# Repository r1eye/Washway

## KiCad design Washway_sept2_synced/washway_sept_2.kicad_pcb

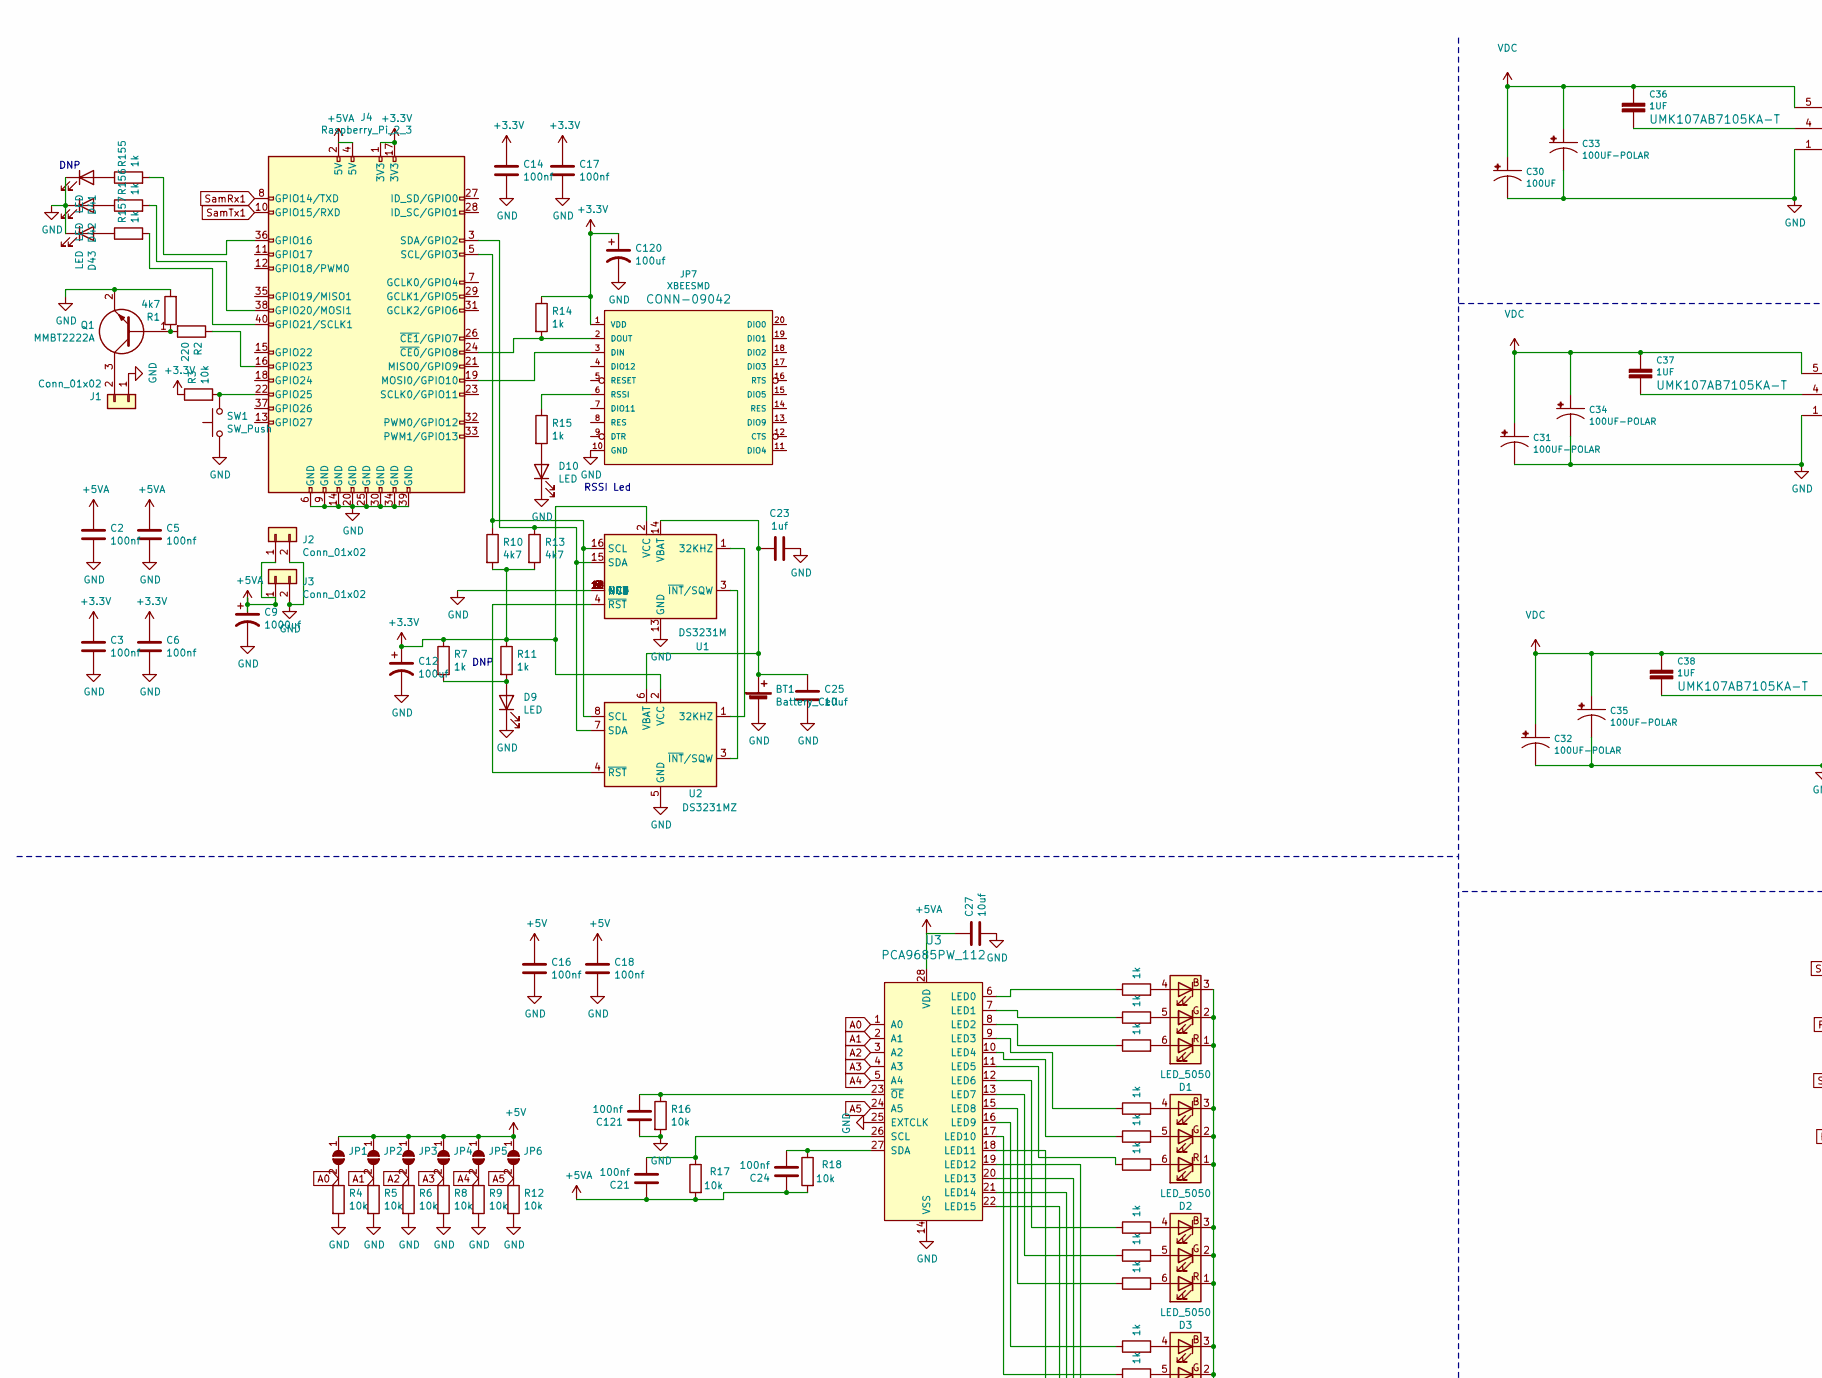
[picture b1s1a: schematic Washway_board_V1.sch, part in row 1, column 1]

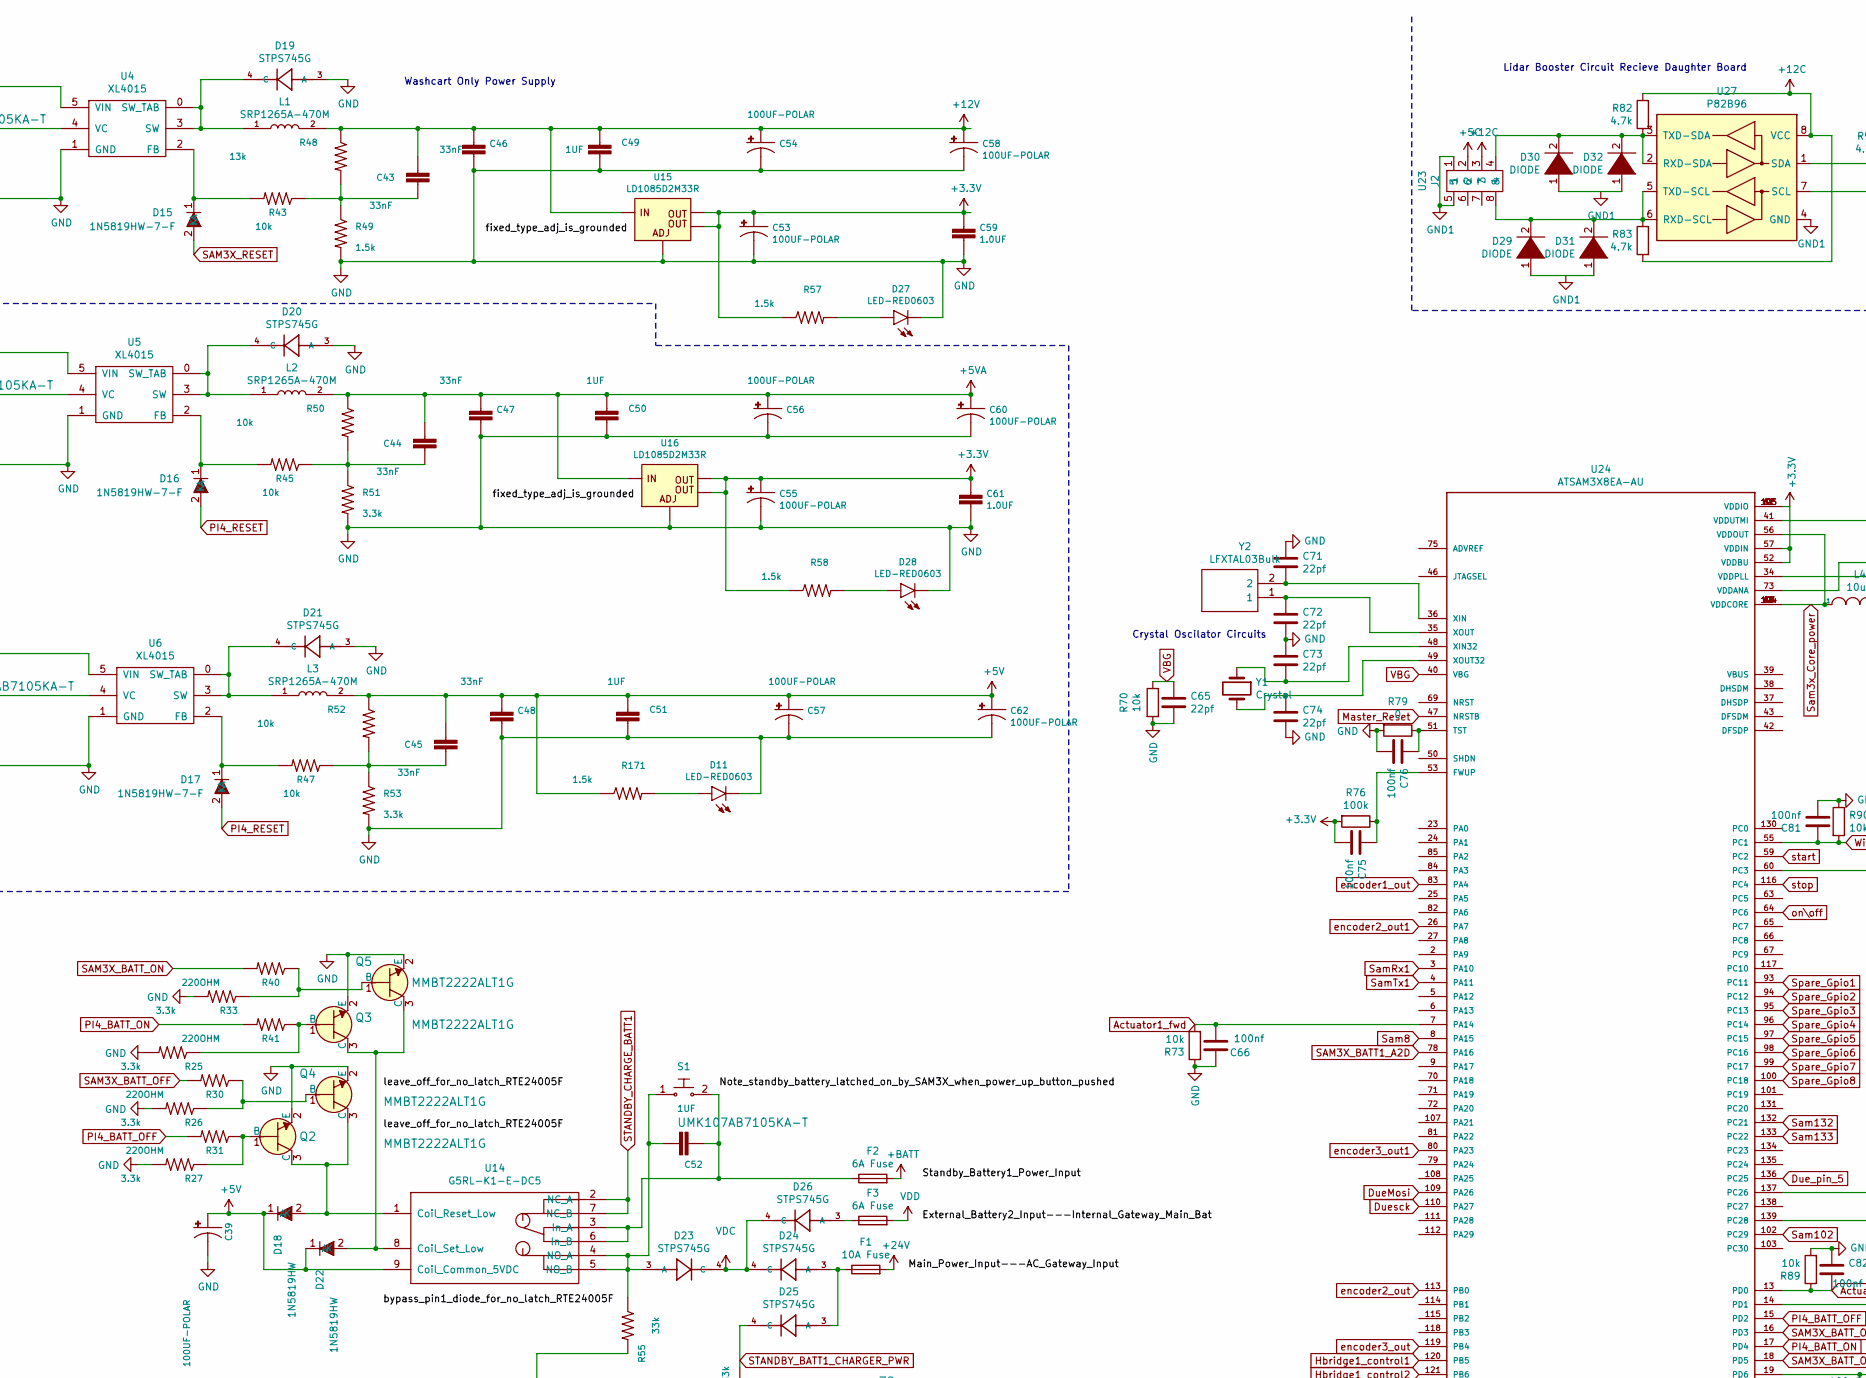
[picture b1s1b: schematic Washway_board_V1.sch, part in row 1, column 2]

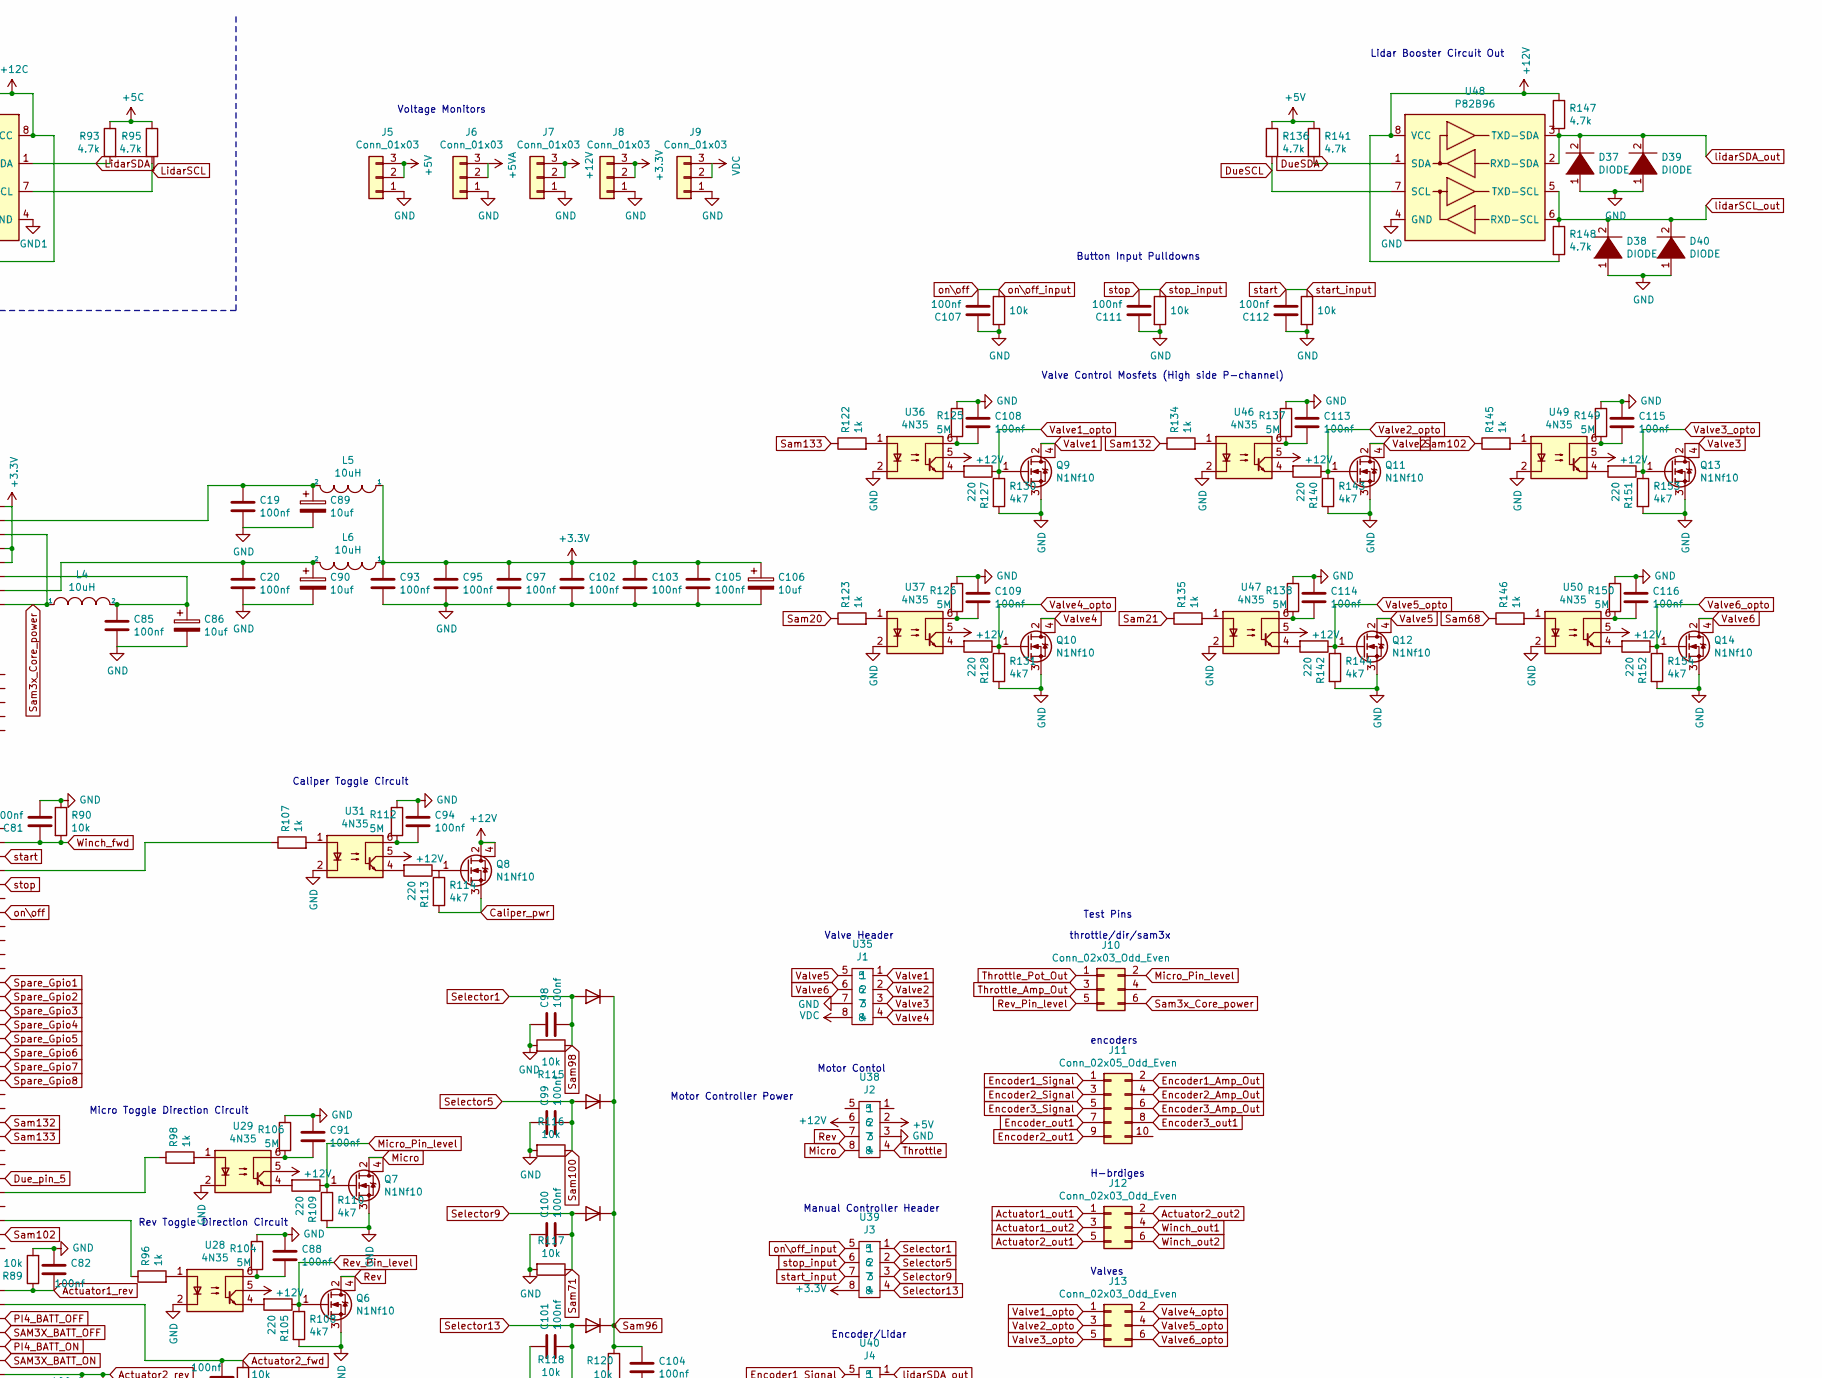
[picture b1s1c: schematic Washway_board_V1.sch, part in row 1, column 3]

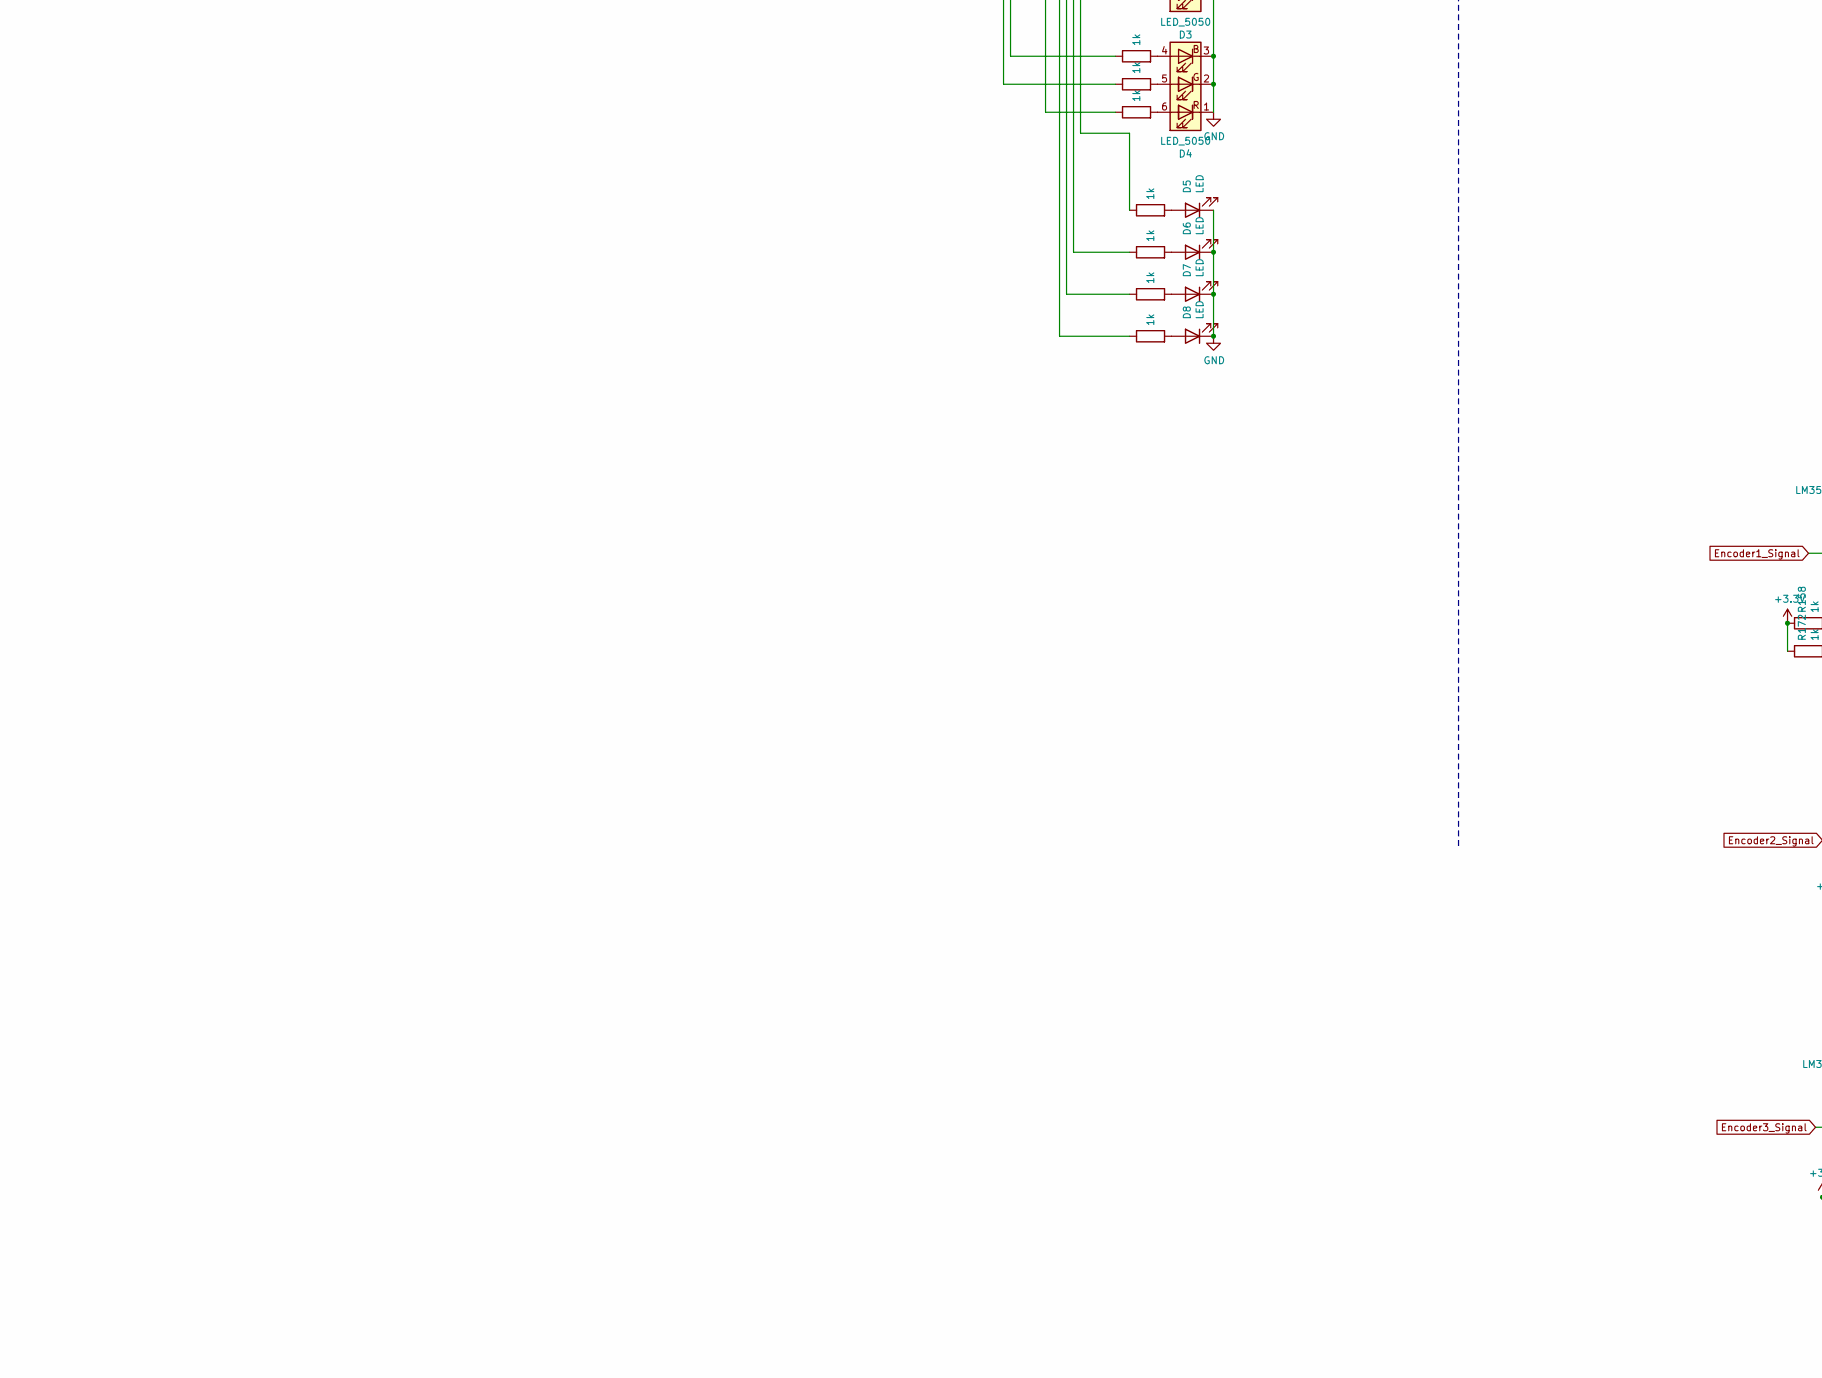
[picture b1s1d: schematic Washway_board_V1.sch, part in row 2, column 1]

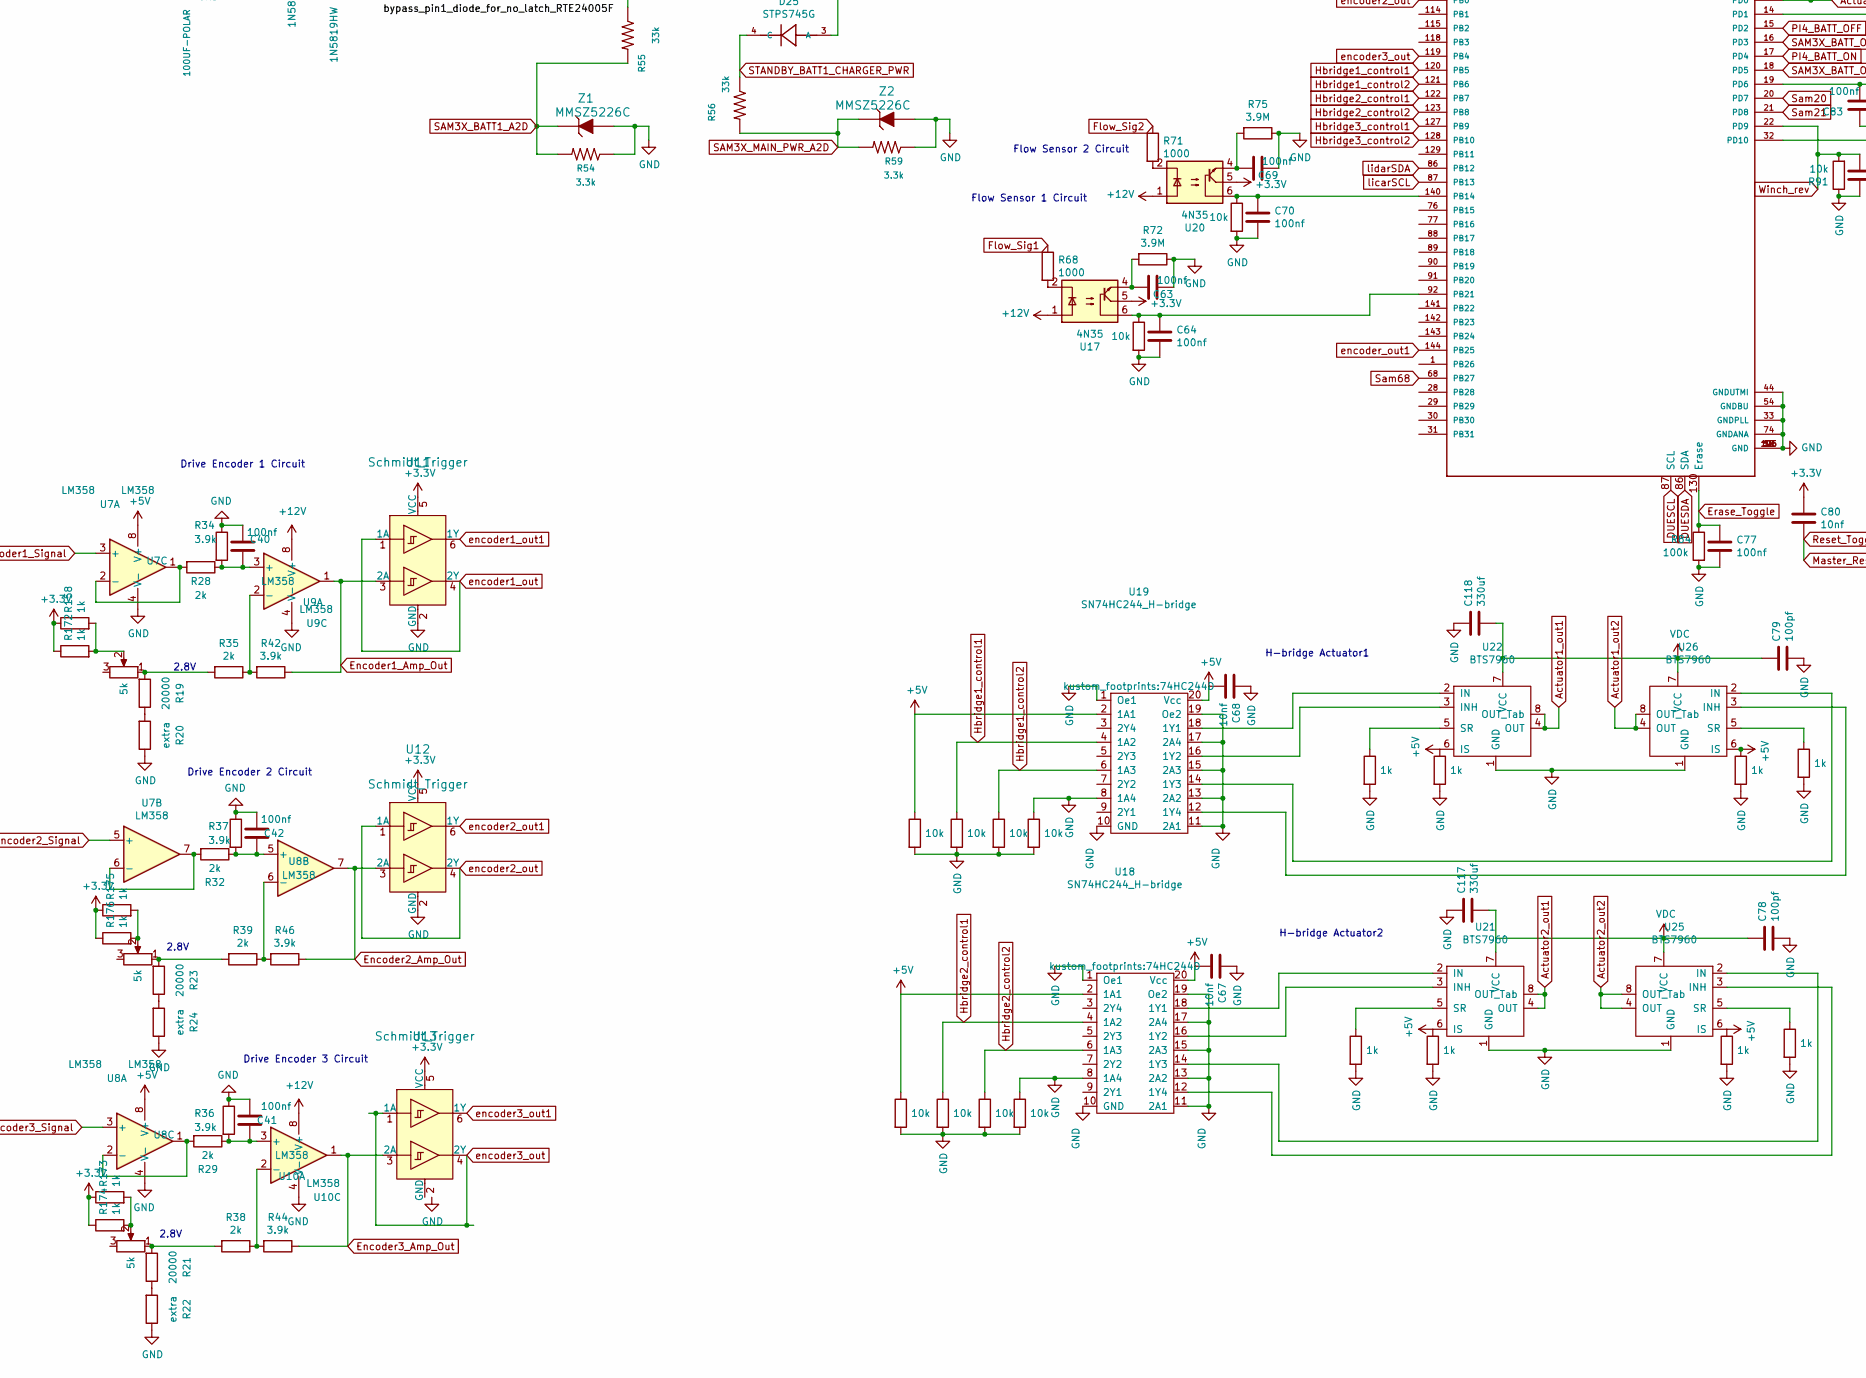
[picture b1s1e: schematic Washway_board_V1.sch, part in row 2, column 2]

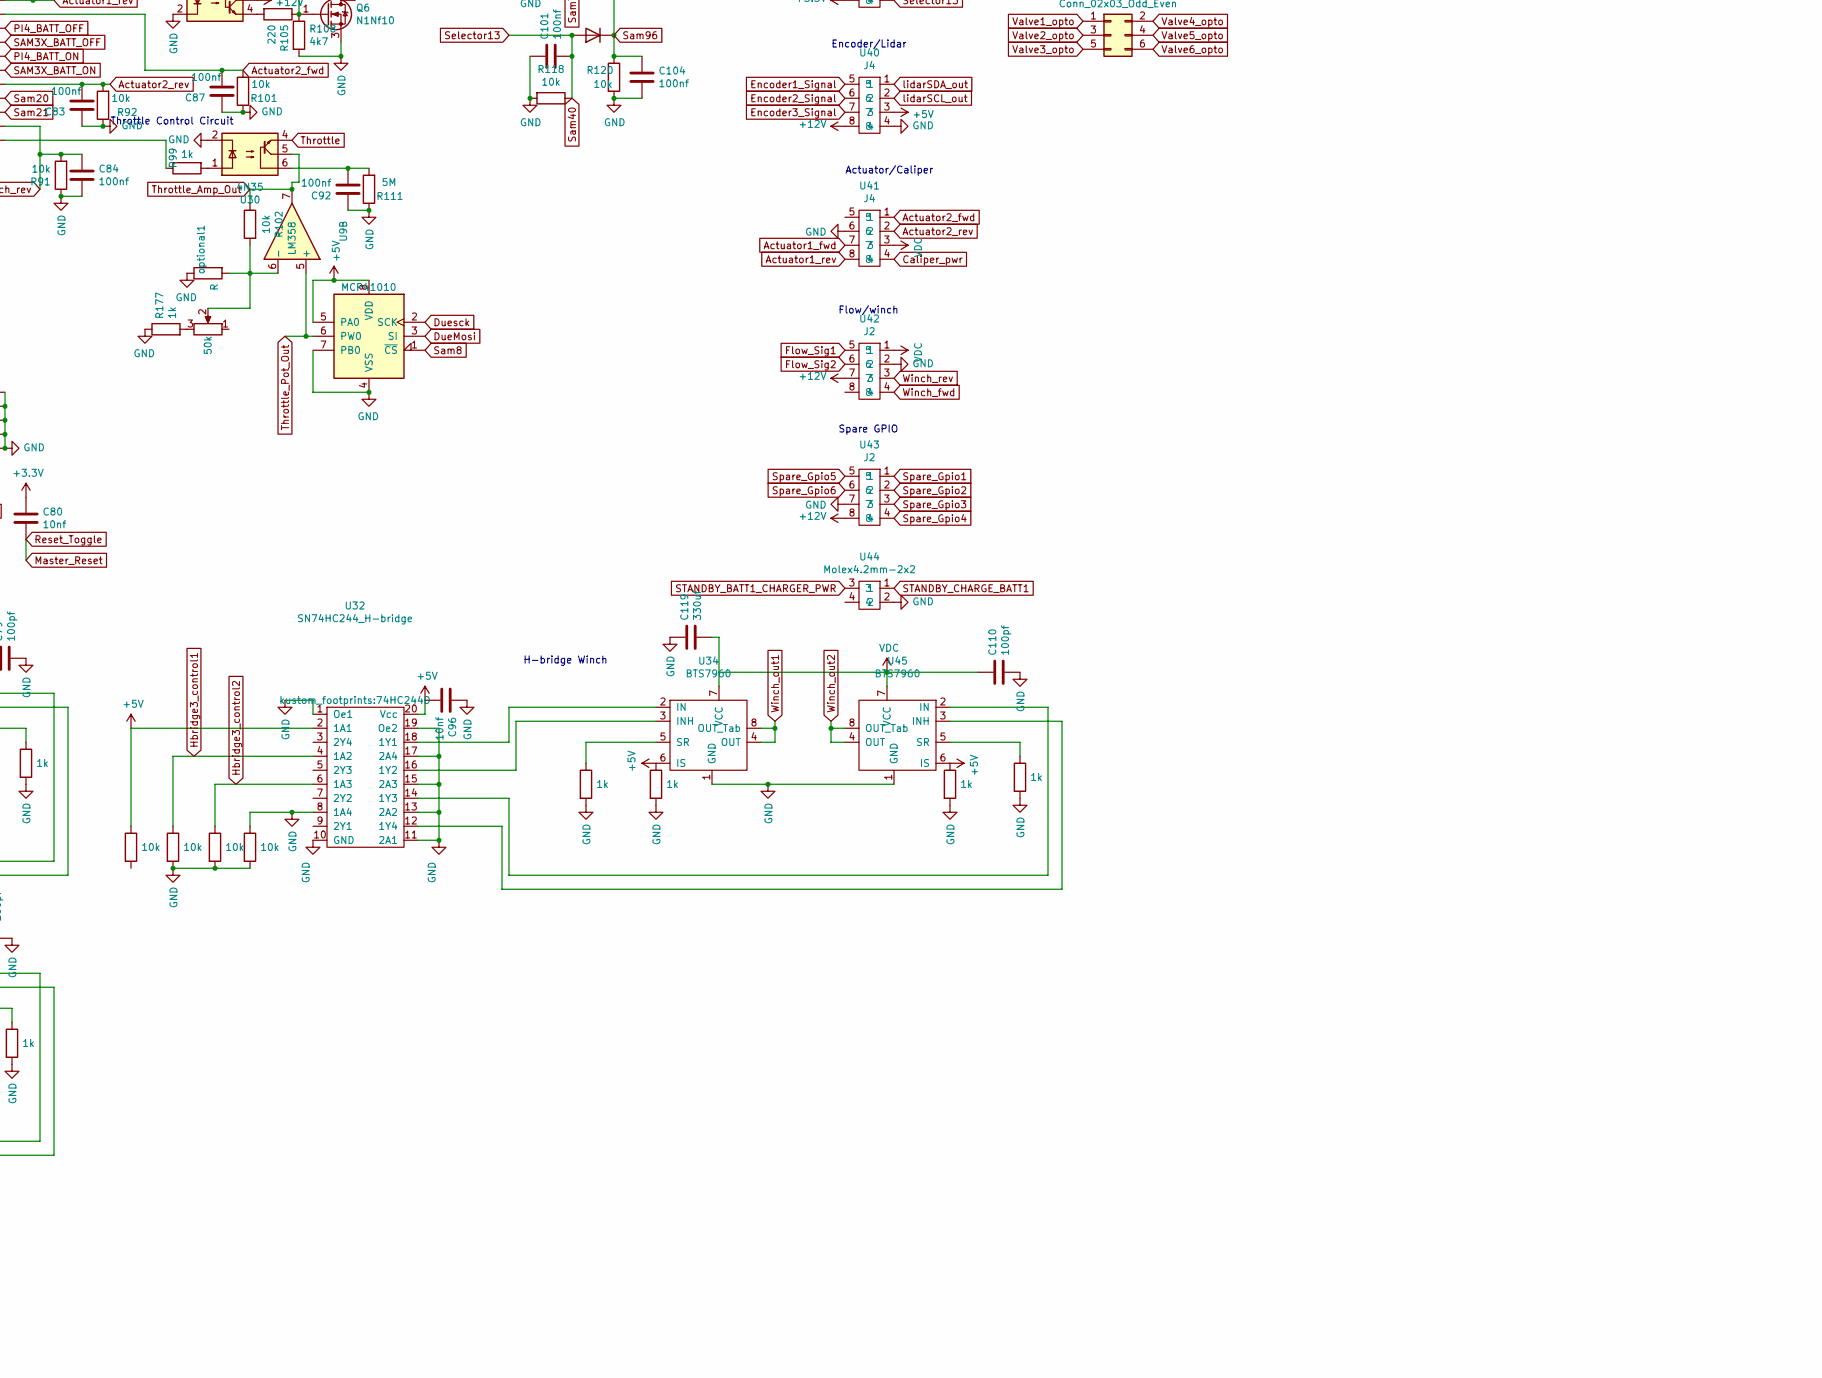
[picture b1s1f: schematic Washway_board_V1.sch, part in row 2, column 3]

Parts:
BT1: Battery_Cell; 2025_bat_horizontal
C2, C3, C5, C6, C14, C16, C17, C18, C20, C21, C24, C40, C41, C42, C63, C64, C66, C69, C70, C75, C76, C77, C81, C82, C83, C84, C85, C87, C88, C91, C92, C93, C94, C95, C97, C98, C99, C100, C101, C102, C103, C104, C105, C107, C108, C109, C111, C112, C113, C114, C115, C116, C121: 100nf; 100nf_0805
C9: 1000uf; CP_Radial_D8.0mm_P3.80mm
C12, C120: 100uf; 100uf_CP_Radial_D10.0mm_P5.00mm
C19: 100nf; 100uf_CP_Radial_D10.0mm_P5.00mm
C23: 1uf; 1uf_0805
C25, C106: 10uf; 10uf_2816_7142_3.20x4.45
C27, C86, C89, C90: 10uf; 10uf_0805
C30: 100UF; 100uf_CP_Radial_D10.0mm_P5.00mm
C31, C32, C33, C34, C35, C39, C53, C54, C55, C56, C57, C58, C60, C62: 100UF-POLAR; 100uf_CP_Radial_D10.0mm_P5.00mm
C36, C37, C38, C49, C50, C51, C52: 1UF; 1uf_0805
C43, C44, C45, C46, C47, C48: 33nF; 33nf_0805
C59, C61: 1.0UF; 1uf_0805
C65, C71, C72, C73, C74: 22pf; 22pf_0805
C67, C68, C80, C96: 10nf; 10nf_0805
C78, C79, C110: 100pf; 100pf_0805
C117, C118, C119: 330uf; 330uf_CP_Radial_D10.0mm_P5.00mm
D1, D2, D3, D4: LED_5050; LED_RGB_5050-6
D5, D6, D7, D8, D9, D41, D42, D43: LED; Led_0805
D10: LED; LED_D5.0mm
D11, D27, D28: LED-RED0603; Led_0805
D15, D16, D17: 1N5819HW-7-F; D_SMA_SS510; MPN 1N5819HW-7-F; Digi-Key_PN 1N5819HW-FDICT-ND
D18: 1N5819HW; D_SMA_SS510; MPN 1N5819HW-7-F; Digi-Key_PN 1N5819HW-FDICT-ND
D19, D20, D21, D23, D24, D25, D26: STPS745G; TO254P1543X460-3N
D22: 1N5819HW; D_SMA; MPN 1N5819HW-7-F; Digi-Key_PN 1N5819HW-FDICT-ND
D29, D30, D31, D32, D37, D38, D39, D40: DIODE; D_SMA_SS510
D33, D34, D35, D36: D; D_SMA_SS510
F1: 10A Fuse; Fuse_2512_6332Metric
F2, F3: 6A Fuse; Fuse_2512_6332Metric
J1: Conn_01x02; PinHeader_1x02_P2.00mm_Vertical
J2: Conn_01x02; fan_2.00mm_header
J3: Conn_01x02; fan_header_2.54header
J4: Raspberry_Pi_2_3; pi_connector
J5, J6: Conn_01x03; Voltage_5v_header
J7: Conn_01x03; Voltage_12v_header
J8: Conn_01x03; Voltage_3.3v_header
J9: Conn_01x03; Voltage_24v_header
J10: Conn_02x03_Odd_Even; throttle_dir_sam3x
J11: Conn_02x05_Odd_Even; Encoders_tester
J12: Conn_02x03_Odd_Even; H_bridges_tester
J13: Conn_02x03_Odd_Even; Valves_tester
JP1, JP2, JP3, JP4, JP5, JP6: 0_ohm_0805
JP7: XBEESMD; xbee_gateway_header
L1, L2, L3: SRP1265A-470M; IND_SRP1265A-330M
L4, L5, L6: 10uH; 10uH_1812_4532
P1, P2, P3: 5k; 5k_trim
P4: 50k; 50k_trim
Q1: MMBT2222A; SOT-23-3; Mouser Part Number 512-MMBT2222A
Q2, Q3, Q4, Q5: MMBT2222ALT1G; SOT-23-3; MPN MMBT2222ALT1G; Digi-Key_PN MMBT2222ALT1GOSCT-ND
Q6, Q7, Q8, Q9, Q10, Q11, Q12, Q13, Q14: N1Nf10; N1Nf10_SOT23
R1, R10, R13, R108, R110, R114, R130, R131, R143, R144, R153, R154: 4k7; 4.7k_0805
R2, R105, R109, R113, R127, R128, R140, R142, R151, R152: 220; 220_0805
R3, R4, R5, R6, R8, R9, R12, R16, R17, R18, R43, R45, R47, R50, R52, R60, R61, R62, R63, R64, R65, R66, R67, R69, R70, R73, R74, R89, R90, R91, R92, R94, R97, R100, R101, R102, R103, R115, R116, R117, R118, R120, R129, R133, R139: 10k; 10k_0805
R7, R11, R14, R15, R77, R78, R80, R81, R85, R86, R87, R88, R96, R98, R99, R107, R119, R121, R122, R123, R124, R132, R134, R135, R145, R146, R155, R156, R157, R158, R159, R160, R161, R162, R163, R164, R165, R166, R167, R168, R169, R170, R172, R173, R174, R175, R176, R177, R178, R179, R180, R181: 1k; 1k_0805
R19, R21, R23: 20000; 20k_0805
R20, R22, R24: extra; extra_0805
R25, R26, R27, R33, R51, R53, R54, R59: 3.3k; 3.3k_0805
R28, R29, R32, R35, R38, R39: 2k; 2k_0805
R30, R31, R40, R41: 220OHM; 220_0805
R34, R36, R37, R42, R44, R46: 3.9k; 3.9k_0805
R48: 13k; 13k_0805
R49, R57, R58, R171: 1.5k; 1.5k_0805
R55, R56: 33k; 33k_0805
R68, R71: 1000; 1k_0805
R72: 3.9M; 3.9k_0805
R75: 3.9M; 3.9M_0805
R76, R84: 100k; 100k_0805
R79: 0; 0_ohm_0805
R82, R83, R93, R95, R136, R141, R147, R148: 4.7k; 4.7k_0805
R104, R106, R111, R112, R125, R126, R137, R138, R149, R150: 5M; 5M_0805
S1: GPTS203211B; on_button; MPN GPTS203211B; Digi-Key_PN CW181-ND
SW1: SW_Push; Switch_Tactile_SMD_4.5x4.5mm_TL3315NF160Q
U1: DS3231M
U2: DS3231MZ; DS323
U3: PCA9685PW_112; TSSOP-28_W4.40mm; MPN PCA9685PW,112; Digi-Key_PN 568-8366-5-ND
U4, U5, U6: XL4015; xl4015
U7, U8, U9, U10: LM358; SOIC8_150MIL
U11, U12, U13: Schmidt_Trigger; Schmidt_trigger; MPN SN74LVC2G17DBVR; Digi-Key_PN 296-13012-1-ND
U14: G5RL-K1-E-DC5
U15, U16: LD1085D2M33R; D2PAK_M
U17, U20, U28, U29, U30, U31, U36, U37, U46, U47, U49, U50: 4N35; 4N35_smd
U18, U19, U32: SN74HC244_H-bridge; 74HC244D
U21, U22, U25, U26, U34, U45: BTS7960
U23, U38, U42, U43: J2; Molex_jr_4.2_2x4
U24: ATSAM3X8EA-AU; QFP50P2200X2200X145-144N
U27, U48: P82B96
U33: MCP41010; mcp413
U35: J1; Molex_jr_4.2_2x4
U39: J3; Molex_jr_4.2_2x4
U40, U41: J4; Molex_jr_4.2_2x4
U44: Molex4.2mm-2x2; 2X2_molex
Y1: Crystal; cfs-206_crystal
Y2: LFXTAL03Bulk; Lfxtal_crystal; Mouser Part Number 449-LFXTAL058383BULK
Z1, Z2: MMSZ5226C; MMSZ5226c_3.3V_zener; MPN MMSZ5231B-7-F; Digi-Key_PN MMSZ5231B-FDICT-ND
optional1: R; R_0805_2012Metric

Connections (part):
+3V3: C3.1, C6.1, C12.1, C14.1, C17.1, C53.1 (+), C55.1 (+), C59.1, C61.1, C75.2, C80.1, C93.1, C95.1, C97.1, C102.1, C103.1, C105.1, C106.1, C120.1, J4.1 (3V3), J4.17 (3V3), J8.2, J8.3, JP7.1 (VDD), L5.1, L6.1, R3.1, R7.1, R10.2, R11.1, R13.2, R14.1, R57.1, R58.1, R76.2, R158.1, R172.1, R173.1, R174.1, R175.1, R176.1, U1.2 (VCC), U2.2 (VCC), U11.5 (VCC), U12.5 (VCC), U13.5 (VCC), U15.2 (OUT), U16.2 (OUT), U17.5, U20.5, U24.11 (VDDIO), U24.52 (VDDBU), U24.57 (VDDIN), U24.62 (VDDIO), U24.105 (VDDIO), U24.125 (VDDIO), U39.8
+5C: R93.1, R95.1, U23.2
+5V: C16.1, C18.1, C39.1 (+), C45.1, C48.1, C51.1, C57.1 (+), C62.1 (+), C67.2, C68.2, C96.2, D18.1 (K), D22.1 (K), J5.2, J5.3, JP1.1 (A), JP2.1 (A), JP3.1 (A), JP4.1 (A), JP5.1 (A), JP6.1 (A), L3.2, R52.1, R60.1, R61.1, R80.1, R81.1, R85.1, R86.1, R94.1, R121.1, R124.1, R136.1, R141.1, R171.1, U7.8 (V+), U8.8 (V+), U14.9 (Coil_Common_5VDC), U18.2 (1A1), U18.20 (Vcc), U19.2 (1A1), U19.20 (Vcc), U21.6 (IS), U22.6 (IS), U25.6 (IS), U26.6 (IS), U32.2 (1A1), U32.20 (Vcc), U33.5 (PA0), U33.8 (VDD), U34.6 (IS), U38.2, U40.3, U45.6 (IS)
+5VA: C2.1, C5.1, C9.1, C21.1, C24.1, C27.1, C44.1, C47.1, C50.1, C56.1 (+), C60.1 (+), J2.1, J3.1, J4.2 (5V), J4.4 (5V), J6.2, J6.3, L2.2, R17.2, R18.2, R50.1, U3.28 (VDD), U16.3 (IN)
+12C: R82.1, R83.2, U23.3, U27.8 (VCC)
+12V: C43.1, C46.1, C49.1, C54.1 (+), C58.1 (+), J7.2, J7.3, L1.2, Q8.2 (D), Q8.4 (Tab), R48.1, R147.1, R148.2, U9.8 (V+), U10.8 (V+), U15.3 (IN), U17.1, U20.1, U28.5, U29.5, U31.5, U36.5, U37.5, U38.6, U40.8, U42.7, U43.8, U46.5, U47.5, U48.8 (VCC), U49.5, U50.5
+24V: F1.2
+BATT: F2.2
A0: JP1.2 (B), R4.1, U3.1 (A0)
A1: JP2.2 (B), R5.1, U3.2 (A1)
A2: JP3.2 (B), R6.1, U3.3 (A2)
A3: JP4.2 (B), R8.1, U3.4 (A3)
A4: JP5.2 (B), R9.1, U3.5 (A4)
A5: JP6.2 (B), R12.1, U3.24 (A5)
Actuator1_fwd: C66.2, R73.2, U24.7 (PA14), U41.7
Actuator1_out1: J12.1, U22.4 (OUT), U22.8 (OUT_Tab)
Actuator1_out2: J12.3, U26.4 (OUT), U26.8 (OUT_Tab)
Actuator1_rev: C82.2, R89.1, U24.13 (PD0), U41.8
Actuator2_fwd: C87.2, R101.2, U24.14 (PD1), U41.1
Actuator2_out1: J12.5, U21.4 (OUT), U21.8 (OUT_Tab)
Actuator2_out2: J12.2, U25.4 (OUT), U25.8 (OUT_Tab)
Actuator2_rev: C83.2, R92.2, U24.19 (PD6), U41.2
Caliper_pwr: Q8.3 (S), R114.2, U41.4
DueMosi: U24.109 (PA26), U33.3 (SI)
DueSCL: R136.2, U48.7 (SCL)
DueSDA: R141.2, U48.1 (SDA)
Due_pin_5: U24.136 (PC25)
Duesck: U24.110 (PA27), U33.2 (SCK)
Encoder1_Amp_Out: J11.2, R42.1, U9.1, U11.3 (2A)
Encoder1_Signal: J11.1, U7.3 (+), U40.5
Encoder2_Amp_Out: J11.4, R46.1, U8.7, U12.3 (2A)
Encoder2_Signal: J11.3, U7.5 (+), U40.6
Encoder2_out1: J11.9
Encoder3_Amp_Out: J11.6, R44.1, U10.1, U13.3 (2A)
Encoder3_Signal: J11.5, U8.3 (+), U40.7
Encoder3_out1: J11.8
Encoder_out1: J11.7
Flow_Sig1: R68.1, U42.5
Flow_Sig2: R71.1, U42.6
GND: BT1.2 (-), C2.2, C3.2, C5.2, C6.2, C9.2, C12.2, C14.2, C16.2, C17.2, C18.2, C19.2, C20.2, C23.1, C25.2, C27.2, C30.2 (-), C31.2 (-), C32.2 (-), C33.2 (-), C34.2 (-), C35.2 (-), C39.2 (-), C40.2, C41.2, C42.2, C46.2, C47.2, C48.2, C49.2, C50.2, C51.2, C53.2 (-), C54.2 (-), C55.2 (-), C56.2 (-), C57.2 (-), C58.2 (-), C59.2, C60.2 (-), C61.2, C62.2 (-), C63.2, C64.2, C65.2, C66.1, C67.1, C68.1, C69.2, C70.2, C71.1, C72.1, C73.1, C74.1, C76.2, C77.2, C78.2, C79.2, C81.2, C82.1, C83.1, C84.2, C85.2, C86.2, C87.1, C88.1, C89.2, C90.2, C91.1, C92.1, C93.2, C94.1, C95.2, C96.1, C97.2, C98.1, C99.1, C100.1, C101.1, C102.2, C103.2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
Hbridge1_control1: R63.1, U19.4 (1A2), U24.120 (PB5)
Hbridge1_control2: R65.1, U19.6 (1A3), U24.121 (PB6)
Hbridge2_control1: R62.1, U18.4 (1A2), U24.122 (PB7)
Hbridge2_control2: R64.1, U18.6 (1A3), U24.123 (PB8)
Hbridge3_control1: R97.1, U24.127 (PB9), U32.4 (1A2)
Hbridge3_control2: R100.1, U24.128 (PB10), U32.6 (1A3)
LidarSCL: R95.2, U27.7 (SCL)
LidarSDA: R93.2, U27.1 (SDA)
Master_Reset: C80.2, U24.47 (NRSTB)
Micro: Q7.2 (D), Q7.4 (Tab), U38.8
Micro_Pin_level: J10.2, Q7.1 (G), R109.1, R110.1
unnamed: BT1.1 (+), C23.2, C25.1, U1.14 (VBAT), U2.6 (VBAT)
unnamed: C19.1, C89.1, L5.2, U24.41 (VDDUTMI)
unnamed: C20.1, C90.1, L6.2, U24.73 (VDDANA)
unnamed: C21.2, R17.1, U3.26 (SCL)
unnamed: C24.2, R18.1, U3.27 (SDA)
unnamed: C36.2, U4.4 (VC)
unnamed: C37.2, U5.4 (VC)
unnamed: C38.2, U6.4 (VC)
unnamed: C40.1, R28.1, R34.2, U9.3 (+)
unnamed: C41.1, R29.1, R36.2, U10.3 (+)
unnamed: C42.1, R32.1, R37.2, U8.5 (+)
unnamed: C43.2, R43.1, R48.2, R49.1
unnamed: C44.2, R45.1, R50.2, R51.1
unnamed: C45.2, R47.1, R52.2, R53.1
unnamed: C52.1, F2.1, S1.2, U14.3 (In_A), U14.6 (In_B)
unnamed: C52.2, D23.3 (A), R55.1, S1.1, U14.4 (NO_A), U14.5 (NO_B)
unnamed: C63.1, R72.2, U17.4
unnamed: C64.1, R69.1, U17.6, U24.92 (PB21)
unnamed: C69.1, R75.2, U20.4
unnamed: C70.1, R74.1, U20.6, U24.140 (PB14)
unnamed: C71.2, U24.36 (XIN), Y2.2
unnamed: C72.2, U24.35 (XOUT), Y2.1
unnamed: C73.2, U24.48 (XIN32), Y1.1
unnamed: C74.2, U24.49 (XOUT32), Y1.2
unnamed: C75.1, R76.1, U24.53 (FWUP)
unnamed: C76.1, R79.1, U24.51 (TST)
unnamed: C85.1, C86.1, L4.2, U24.34 (VDDPLL)
unnamed: C88.2, R104.2, U28.6
unnamed: C91.2, R106.2, U29.6
unnamed: C92.2, R111.2, U30.6
unnamed: C94.2, R112.2, U31.6
unnamed: C108.2, R125.2, U36.6
unnamed: C109.2, R126.2, U37.6
unnamed: C113.2, R137.2, U46.6
unnamed: C114.2, R138.2, U47.6
unnamed: C115.2, R149.2, U49.6
unnamed: C116.2, R150.2, U50.6
unnamed: C117.2, U21.7 (VCC)
unnamed: C121.2, R16.1, U3.23 (~OE)
unnamed: D1.4 (BA), R159.2
unnamed: D1.5 (GA), R160.2
unnamed: D1.6 (RA), R161.2
unnamed: D2.4 (BA), R162.2
unnamed: D2.5 (GA), R163.2
unnamed: D2.6 (RA), R164.2
unnamed: D3.4 (BA), R165.2
unnamed: D3.5 (GA), R166.2
unnamed: D3.6 (RA), R167.2
unnamed: D4.4 (BA), R168.2
unnamed: D4.5 (GA), R169.2
unnamed: D4.6 (RA), R170.2
unnamed: D5.2 (A), R178.2
unnamed: D6.2 (A), R179.2
unnamed: D7.2 (A), R180.2
unnamed: D8.2 (A), R181.2
unnamed: D9.2 (A), R7.2, R11.2
unnamed: D10.2 (A), R15.2
unnamed: D11.1 (A), R171.2
unnamed: D15.1 (K), R43.2, U4.2 (FB)
unnamed: D16.1 (K), R45.2, U5.2 (FB)
unnamed: D17.1 (K), R47.2, U6.2 (FB)
unnamed: D18.2 (A), Q2.3 (C), Q4.3 (C), U14.1 (Coil_Reset_Low)
unnamed: D19.4 (C), L1.1, U4.0 (SW_TAB), U4.3 (SW)
unnamed: D20.4 (C), L2.1, U5.0 (SW_TAB), U5.3 (SW)
unnamed: D21.4 (C), L3.1, U6.0 (SW_TAB), U6.3 (SW)
unnamed: D22.2 (A), Q3.3 (C), Q5.3 (C), U14.8 (Coil_Set_Low)
unnamed: D24.3 (A), D25.3 (A), F1.1
unnamed: D26.3 (A), F3.1
unnamed: D27.1 (A), R57.2
unnamed: D28.1 (A), R58.2
unnamed: D29.2 (A), D31.2 (A), R83.1, U23.8, U27.5 (TXD-SCL), U27.6 (RXD-SCL)
unnamed: D30.2 (A), D32.2 (A), R82.2, U23.4, U27.2 (RXD-SDA), U27.3 (TXD-SDA)
unnamed: D41.2 (A), R155.1
unnamed: D42.2 (A), R156.1
unnamed: D43.2 (A), R157.1
unnamed: J1.2, Q1.3
unnamed: J4.3 (SDA/GPIO2), R13.1, U1.15 (SDA), U2.7 (SDA)
unnamed: J4.5 (SCL/GPIO3), R10.1, U1.16 (SCL), U2.8 (SCL)
unnamed: J4.16 (GPIO23), R2.1
unnamed: J4.19 (MOSI0/GPIO10), JP7.3 (DIN)
unnamed: J4.22 (GPIO25), R3.2, SW1.2
unnamed: J4.24 (~CE0~/GPIO8), JP7.2 (DOUT), R14.2
unnamed: J4.36 (GPIO16), R155.2
unnamed: J4.38 (GPIO20/MOSI1), R156.2
unnamed: J4.40 (GPIO21/SCLK1), R157.2
unnamed: JP7.6 (RSSI), R15.1
unnamed: P1.1, R19.2, R35.2
unnamed: P1.2, R158.2, R172.2
unnamed: P2.1, R21.2, R38.2
unnamed: P2.2, R173.2, R174.2
unnamed: P3.1, R23.2, R39.2
unnamed: P3.2, R175.2, R176.2
unnamed: P4.2, R102.2, U9.6 (-), optional1.2
unnamed: P4.3, R177.2
unnamed: Q1.1, R1.1, R2.2
unnamed: Q2.1 (B), R27.1, R31.1
unnamed: Q3.1 (B), R25.1, R41.1
unnamed: Q4.1 (B), R26.1, R30.1
unnamed: Q5.1 (B), R33.1, R40.1
unnamed: Q8.1 (G), R113.1, R114.1
unnamed: R19.1, R20.2
unnamed: R21.1, R22.2
unnamed: R23.1, R24.2
unnamed: R28.2, U7.1, U7.2 (-)
unnamed: R29.2, U8.1, U8.2 (-)
unnamed: R32.2, U7.6 (-), U7.7
unnamed: R35.1, R42.2, U9.2 (-)
unnamed: R38.1, R44.2, U10.2 (-)
unnamed: R39.1, R46.2, U8.6 (-)
unnamed: R68.2, U17.2
unnamed: R71.2, U20.2
unnamed: R77.1, U21.5 (SR)
unnamed: R78.1, U22.5 (SR)
unnamed: R87.1, U25.5 (SR)
unnamed: R88.1, U26.5 (SR)
unnamed: R96.1, U24.139 (PC28)
unnamed: R96.2, U28.1
unnamed: R98.1, U24.137 (PC26)
unnamed: R98.2, U29.1
unnamed: R99.1, U24.32 (PD10)
unnamed: R99.2, U30.1
unnamed: R105.2, U28.4
unnamed: R107.1, U24.60 (PC3)
unnamed: R107.2, U31.1
unnamed: R109.2, U29.4
unnamed: R113.2, U31.4
unnamed: R119.1, U34.5 (SR)
unnamed: R122.2, U36.1
unnamed: R123.2, U37.1
unnamed: R127.2, U36.4
unnamed: R128.2, U37.4
unnamed: R132.1, U45.5 (SR)
unnamed: R134.2, U46.1
unnamed: R135.2, U47.1
unnamed: R140.2, U46.4
unnamed: R142.2, U47.4
unnamed: R145.2, U49.1
unnamed: R146.2, U50.1
unnamed: R151.2, U49.4
unnamed: R152.2, U50.4
unnamed: R159.1, U3.6 (LED0)
unnamed: R160.1, U3.7 (LED1)
unnamed: R161.1, U3.8 (LED2)
unnamed: R162.1, U3.9 (LED3)
unnamed: R163.1, U3.10 (LED4)
unnamed: R164.1, U3.11 (LED5)
unnamed: R165.1, U3.12 (LED6)
unnamed: R166.1, U3.13 (LED7)
unnamed: R167.1, U3.15 (LED8)
unnamed: R168.1, U3.16 (LED9)
unnamed: R169.1, U3.17 (LED10)
unnamed: R170.1, U3.18 (LED11)
unnamed: R178.1, U3.19 (LED12)
unnamed: R179.1, U3.20 (LED13)
unnamed: R180.1, U3.21 (LED14)
unnamed: R181.1, U3.22 (LED15)
unnamed: U1.1 (32KHZ), U2.1 (32KHZ)
unnamed: U1.3 (~INT~/SQW), U2.3 (~INT~/SQW)
unnamed: U1.4 (~RST), U2.4 (~RST)
unnamed: U18.12 (1Y4), U25.3 (INH)
unnamed: U18.14 (1Y3), U25.2 (IN)
unnamed: U18.16 (1Y2), U21.3 (INH)
unnamed: U18.18 (1Y1), U21.2 (IN)
unnamed: U19.12 (1Y4), U26.3 (INH)
unnamed: U19.14 (1Y3), U26.2 (IN)
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
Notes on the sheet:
Throttle Control Circuit
2.8V
Drive Encoder 1 Circuit
Drive Encoder 2 Circuit
Valve Control Mosfets (High side P-channel)
Button Input Pulldowns
Micro Toggle Direction Circuit
Rev Toggle Direction Circuit
Caliper Toggle Circuit
Crystal Oscilator Circuits
Flow Sensor 2 Circuit
Flow Sensor 1 Circuit
Motor Controller Power
Voltage Monitors
RSSI Led
Test Pins
throttle/dir/sam3x
encoders
Valve Header
Motor Contol
Manual Controller Header
Drive Encoder 3 Circuit
H-bridge Actuator1
H-brdiges
Valves
H-bridge Actuator2
H-bridge Winch
Encoder/Lidar
Actuator/Caliper
Flow/winch
Spare GPIO
Lidar Booster Circuit Out
Lidar Booster Circuit Recieve Daughter Board
Washcart Only Power Supply
DNP

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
